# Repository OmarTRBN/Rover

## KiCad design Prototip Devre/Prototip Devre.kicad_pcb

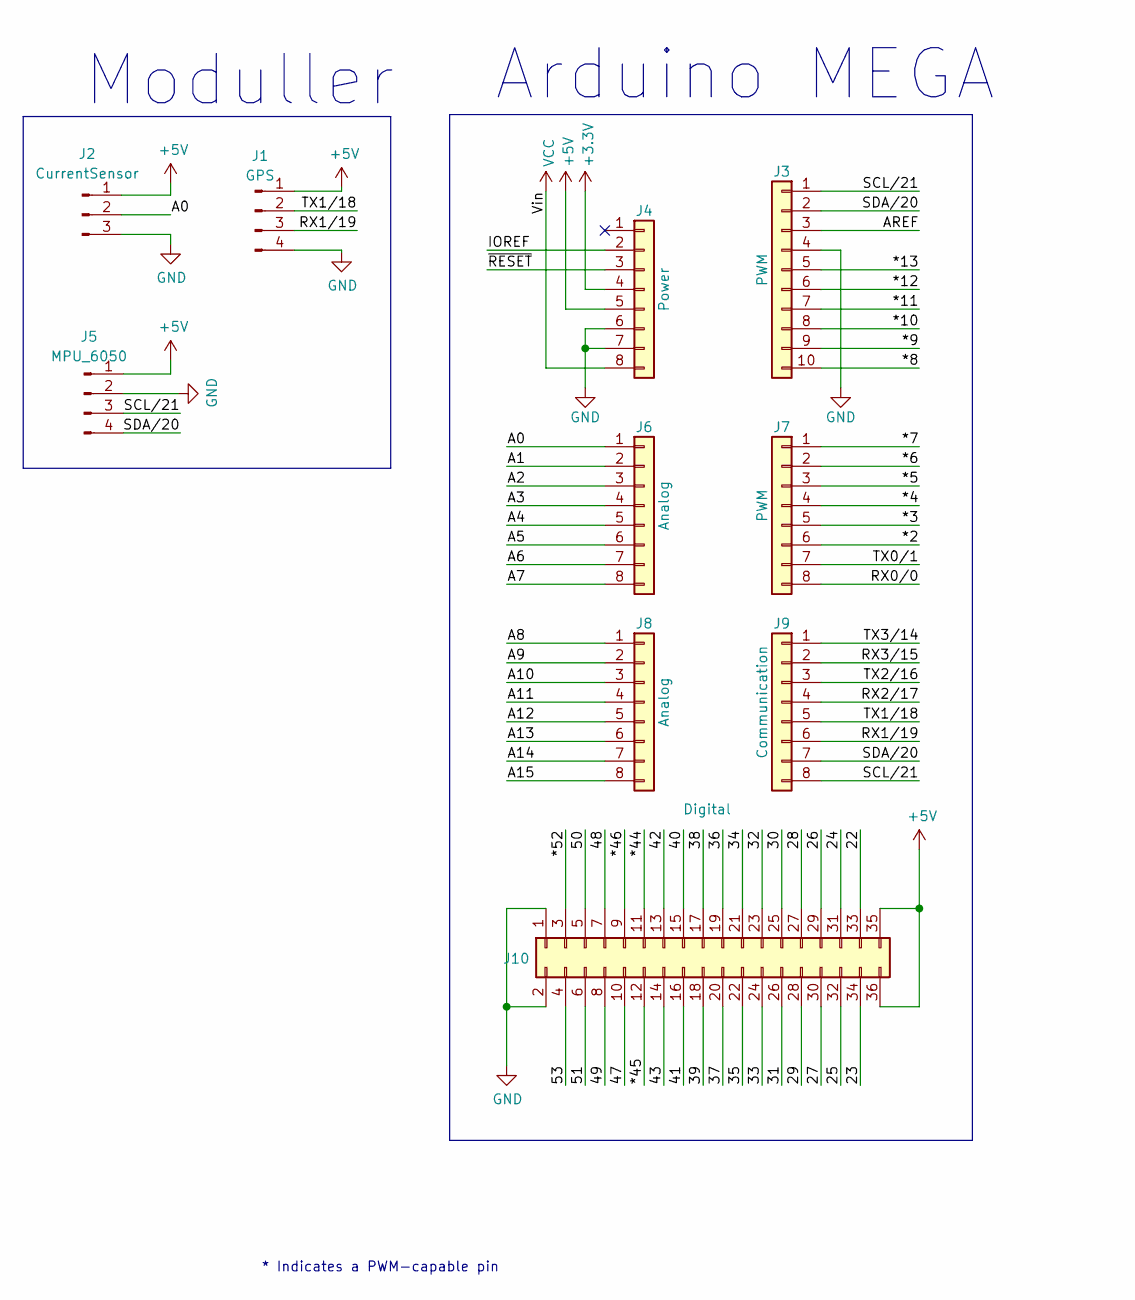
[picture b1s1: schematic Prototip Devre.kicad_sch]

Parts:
J1: GPS; PinHeader_1x04_P2.54mm_Vertical
J2: CurrentSensor
J3: PWM; PinSocket_1x10_P2.54mm_Vertical
J4: Power; PinSocket_1x08_P2.54mm_Vertical
J5: MPU_6050
J6: Analog; PinHeader_1x08_P2.54mm_Vertical
J7: PWM; PinSocket_1x08_P2.54mm_Vertical
J8: Analog; PinSocket_1x08_P2.54mm_Vertical
J9: Communication; PinSocket_1x08_P2.54mm_Vertical
J10: Digital; PinSocket_2x18_P2.54mm_Vertical

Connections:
+3V3: J4.4
+5V: J1.1, J2.1, J4.5, J5.1, J10.35, J10.36
/22: J10.33
/23: J10.34
/24: J10.31
/25: J10.32
/26: J10.29
/27: J10.30
/28: J10.27
/29: J10.28
/30: J10.25
/31: J10.26
/32: J10.23
/33: J10.24
/34: J10.21
/35: J10.22
/36: J10.19
/37: J10.20
/38: J10.17
/39: J10.18
/40: J10.15
/41: J10.16
/42: J10.13
/43: J10.14
/47: J10.10
/48: J10.7
/49: J10.8
/50: J10.5
/51: J10.6
/53: J10.4
/*2: J7.6
/*3: J7.5
/*4: J7.4
/*5: J7.3
/*6: J7.2
/*7: J7.1
/*8: J3.10
/*9: J3.9
/*10: J3.8
/*11: J3.7
/*12: J3.6
/*13: J3.5
/*44: J10.11
/*45: J10.12
/*46: J10.9
/*52: J10.3
/A0: J2.2, J6.1
/A1: J6.2
/A2: J6.3
/A3: J6.4
/A4: J6.5
/A5: J6.6
/A6: J6.7
/A7: J6.8
/A8: J8.1
/A9: J8.2
/A10: J8.3
/A11: J8.4
/A12: J8.5
/A13: J8.6
/A14: J8.7
/A15: J8.8
/AREF: J3.3
/IOREF: J4.2
/RX0/0: J7.8
/RX1/19: J1.3, J9.6
/RX2/17: J9.4
/RX3/15: J9.2
/SCL/21: J3.1, J5.3, J9.8
/SDA/20: J3.2, J5.4, J9.7
/TX0/1: J7.7
/TX1/18: J1.2, J9.5
/TX2/16: J9.3
/TX3/14: J9.1
/~RESET: J4.3
GND: J1.4, J2.3, J3.4, J4.6, J4.7, J5.2, J10.1, J10.2
VCC: J4.8

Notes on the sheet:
Arduino MEGA
* Indicates a PWM-capable pin
Moduller

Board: 2 copper layers, 16 parts (0 on the bottom side), 7 nets, no tracks yet.

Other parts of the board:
MH1, MH2, MH3, MH4, MH5, MH6: MountingHole_3.2mm

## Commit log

2024-07-27 Initial commit.
